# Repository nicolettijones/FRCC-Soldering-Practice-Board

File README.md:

# FRCC Soldering Practice Board

A simple PCB designed by the Front Range Community College Engineering Club intended to teach basic soldering skills. 

## Required Materials

- Soldering iron
- Solder
- Generic through-hole resistor, LED, and 6mmx6mm tactile switch
- CR2032 coin-cell battery
- CR2032 battery holder:
	- This is the specific battery holder that the board through holes were designed around https://a.co/d/0bjY5XxG (non-affiliate link)

## To Order this PCB:

Download the zip file below. You do not need to unzip this file to order the board. 

[Download FRCCWolfPCB.zip](https://raw.githubusercontent.com/nicolettijones/FRCC-Soldering-Practice-Board/main/Zipped%20Gerbers/FRCCWolfPCB.zip)

Using a PCB manufacturer (I used PCBWay to order the test boards for this project), start a new order and select the option to upload gerber files. 

Upload the FRCCWolfPCB.zip file. The pre-selected options should not need to be changed, except you will need to select HASL lead-free solder if you want the lead free option and also specify what solder mask color you want. You will also need to change the order quantity to the desired number. 

When selecting shipping, keep in mind that the actual shipping times (especially for USPS) may be longer than the estimates. The USPS option also does not provide detailed order tracking after the shipment has left China. Also factor in a day or two for the order design to be approved. 

The rest is pretty self-explanatory, but please feel free to reach out if you run into any issues.

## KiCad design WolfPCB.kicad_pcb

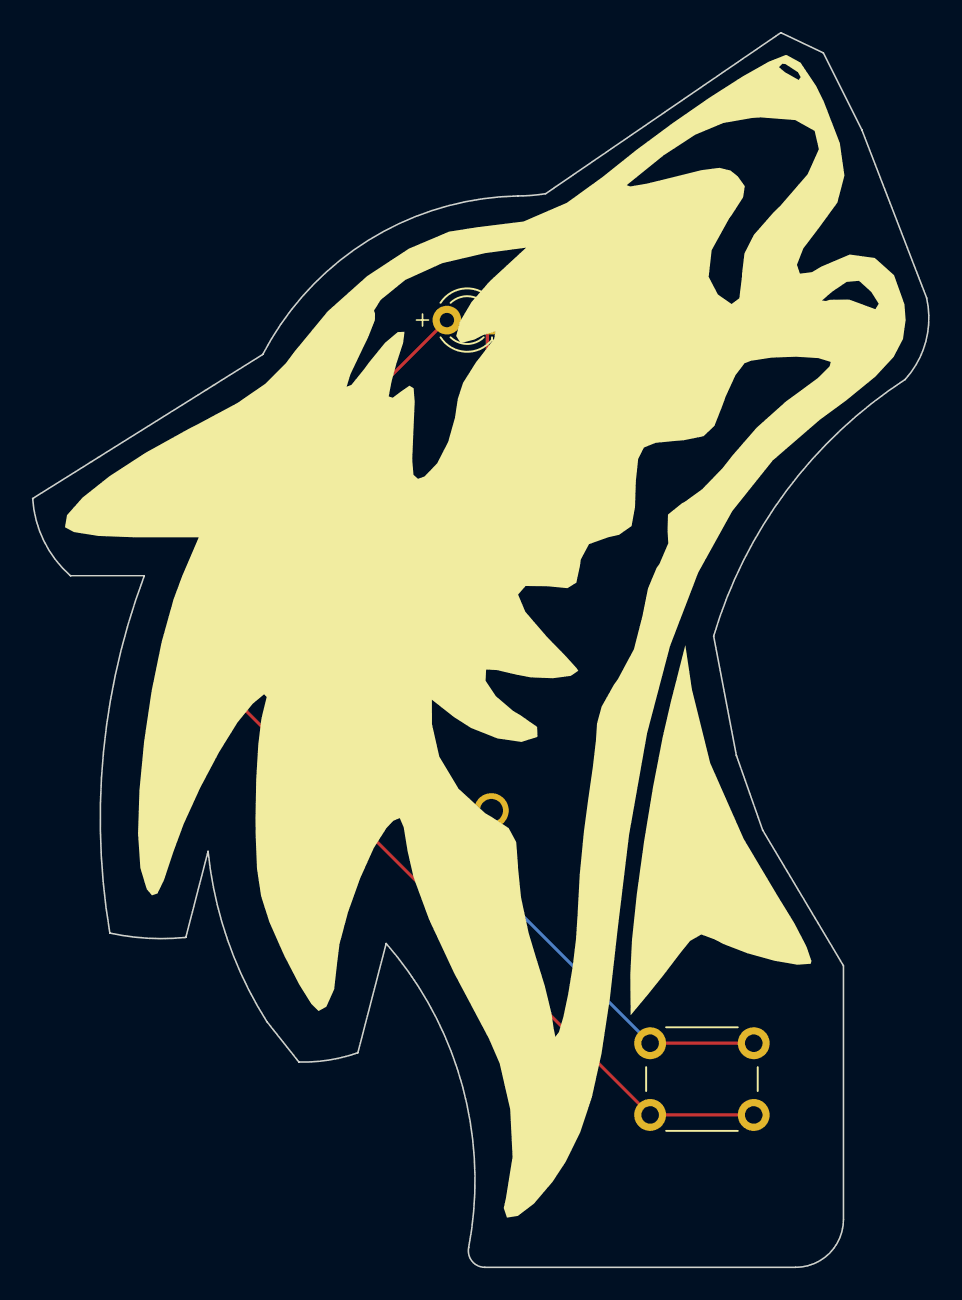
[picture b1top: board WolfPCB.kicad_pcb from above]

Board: 2 copper layers, 56.2 x 77.5 mm, 4 parts (1 on the bottom side), 4 nets.

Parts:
2032 BAT: BS-3; BAT_BS-3
D1: LED; LED_D3.0mm
R1: 100Ω; R_Axial_DIN0207_L6.3mm_D2.5mm_P10.16mm_Horizontal
SW1: SW_Push; SW_PUSH_6mm_H4.3mm

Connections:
unnamed: 2032 BAT.+, SW1.1
unnamed: D1.2 (A), R1.1
unnamed: 2032 BAT.-, D1.1 (K)
unnamed: R1.2, SW1.2

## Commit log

2026-02-23 Add Gerber outputs and KiCad project files
    Exported KiCad project 'WolfPCB' including generated Gerber files (B_Cu, F_Cu, masks, paste, silkscreen, edge cuts, NPTH/PTH drills, .gbrjob and a zipped archive), KiCad project files (.kicad_pcb, .k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
2026-02-23 Rearranged file structure
2026-02-23 Update README with materials and ordering info
    Added required materials and ordering instructions for the PCB.
2026-02-23 Update README with additional PCB ordering details
    Clarified instructions for ordering PCBs and added images.
